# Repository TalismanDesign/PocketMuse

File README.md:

# PocketMuse

Music player app for the PocketMage PDA. Streams MP3 from SD through the OS
audio service, using the built-in PWM piezo or a USB Audio Class speaker.
Supports library browsing, now-playing with album art, playlist management,
shuffle, and loop modes. Runs as a dynamically loaded ELF app on PocketMage OS.

## Build

PocketMuse is an ELF app built against the PocketMage SDK.
Build it with the `pm` CLI from the SDK checkout:

```sh
pm build --pack
```

That compiles `src/`, links `build/PocketMuse.app.elf` plus the
`build/PocketMuse.elfo` overlay, and packs them into `build/PocketMuse.tar`
for installation through the OS app manager. Packaging requires the SDK's
`elf_overlay_relink` and `elf_overlay_emit` tools on `PATH`.

For an ELF-only clean build from this checkout:

```sh
export SDK_ROOT="$(cd ../PocketMage_PDA/Code/PocketMageOS/lib/PocketMage_SDK && pwd)"
make SDK_ROOT="$SDK_ROOT" clean
make SDK_ROOT="$SDK_ROOT" elf
```

The SDK build recipe locates the installed Espressif Xtensa C++ toolchain.
Build the matching host from `PocketMage_PDA/Code/PocketMageOS` with
`pio run -e PM_BETA`. The host must export the playback-request, image-region,
SD-stream, drawing, and activity APIs used by this app.

`mp3` files live in `/music/` at the root of the SD card; the app creates that
directory along with `/music/.muse/` on first launch.

## Key bindings

| Input        | Action                     |
|--------------|----------------------------|
| LEFT / RIGHT | Navigate list / skip track |
| UP / DOWN    | Volume (Now Playing)       |
| SPACE        | Play / pause               |
| ENTER        | Select / play              |
| P            | Cycle source in browser; show queue from Now Playing |
| F            | Toggle favorite            |
| S            | Toggle shuffle             |
| L            | Cycle loop (None/One/All)  |
| D            | Remove selected favorite / playlist entry; keep the music file |
| U            | Output: Auto / Piezo / USB  |
| B            | Switch browser / Now Playing; return from queue |
| ?            | Help overlay               |
| ESC / A      | Exit to PocketMage OS      |

Touch scroll on the slider controls volume in all modes.

## Playback and storage

- Auto selects a connected UAC speaker; Piezo forces the built-in output.
  USB falls back to piezo when no compatible speaker is available. The USB
  status chip appears only while USB is the active playback output.
- Volume and output preference are shared SDK settings in NVS (`PMAudio`). Favorites use
  an absolute-path list; playlists are `.m3u` files under
  `/music/.muse/playlists/`, with one absolute SD path per entry. Blank lines,
  comments, LF, and CRLF are supported. Empty sources remain browsable.
- Natural EOF advances once. Repeat-one affects automatic progression;
  manual next still skips. Shuffle stops after its cycle unless repeat-all
  is enabled. Favorite edits outside the active source preserve the current
  shuffle cycle; a missing playing track keeps the not-found index at `-1`.
- ID3v2.3/v2.4 tags and embedded JPEG/PNG cover regions are read by the SDK's
  streaming media service. The OS decodes covers into a 1-bit image buffer. Unsupported/missing artwork
  uses the app's fallback display.
- The OLED uses decoded PCM frame timing for elapsed playback. Total duration
  comes from MPEG headers, including Xing/VBRI when present, with a bitrate
  estimate when an exact duration is unavailable.
- Idle sleep belongs to the OS and uses its `TIMEOUT` setting. Native and ELF
  input reset the same timer. Playback, open SD streams, USB audio presence,
  USB mode, and OS timeout-inhibition flags keep the device awake.

## Architecture

PocketMuse calls the SDK C ABI; it does not link Arduino or audio/display
drivers. The host owns Espressif `esp_audio_codec`, `pwm_audio`, `usb_stream`,
JPEGDEC/PNGdec, GxEPD2, U8g2, SD access, and sleep management.

Playback queries, metadata/cover probing, image-region decoding, SD operations,
and canvas primitives are generated wrappers over native SDK services. The SDK
owns PCM gain, timing, shared audio settings, and metadata parsing. PocketMuse
owns its library, playlist, shuffle, and presentation state. The SDK retains
ABI 2 adapters for existing apps.

USB serial is the default connector role. Piezo and unattached Auto sessions
retain it; an attached accessory receives one bounded UAC probe. An unsupported
device can then be tried as a keyboard. App exit waits for audio cleanup while
its callbacks and code remain resident.

## Native tests

```sh
python3 tests/run.py
```

Requires Python 3 and a C++17 compiler with AddressSanitizer and UBSan. `CXX`
selects the compiler; `SDK_ROOT` overrides the adjacent SDK checkout. The
tests exercise playlist parsing/mutation, shuffle continuity, playback progression, source
cycling, output preference, playback request results, and idle-timer rollover
and inhibition. They use in-memory SD files and require no device.

USB enumeration/hotplug, audible output, album-art rendering, both displays,
and deep sleep still require validation on a PocketMage device.

## Project layout

```text
src/
   main.cpp             app entry, input and render loop
   muse.cpp             app-wide globals
   library.cpp          SD card track scanner (/music/)
   playlist.cpp         playlist manager (favorites, .m3u)
   ui_player.cpp        playback control, shuffle, shared media-service queries
   ui/
      ui_browser.cpp    library/favorites/playlist browser
      ui_nowplaying.cpp now-playing screen with album art
      ui_playlist.cpp   playlist queue view
      ui_helpers.cpp    header/footer/scrollbar/OLED/time formatting
include/                public headers
tests/                  native regression suites and in-memory SD support
design/                 chosen display mockups
```

## License

Apache-2.0. Same as the PocketMage project.

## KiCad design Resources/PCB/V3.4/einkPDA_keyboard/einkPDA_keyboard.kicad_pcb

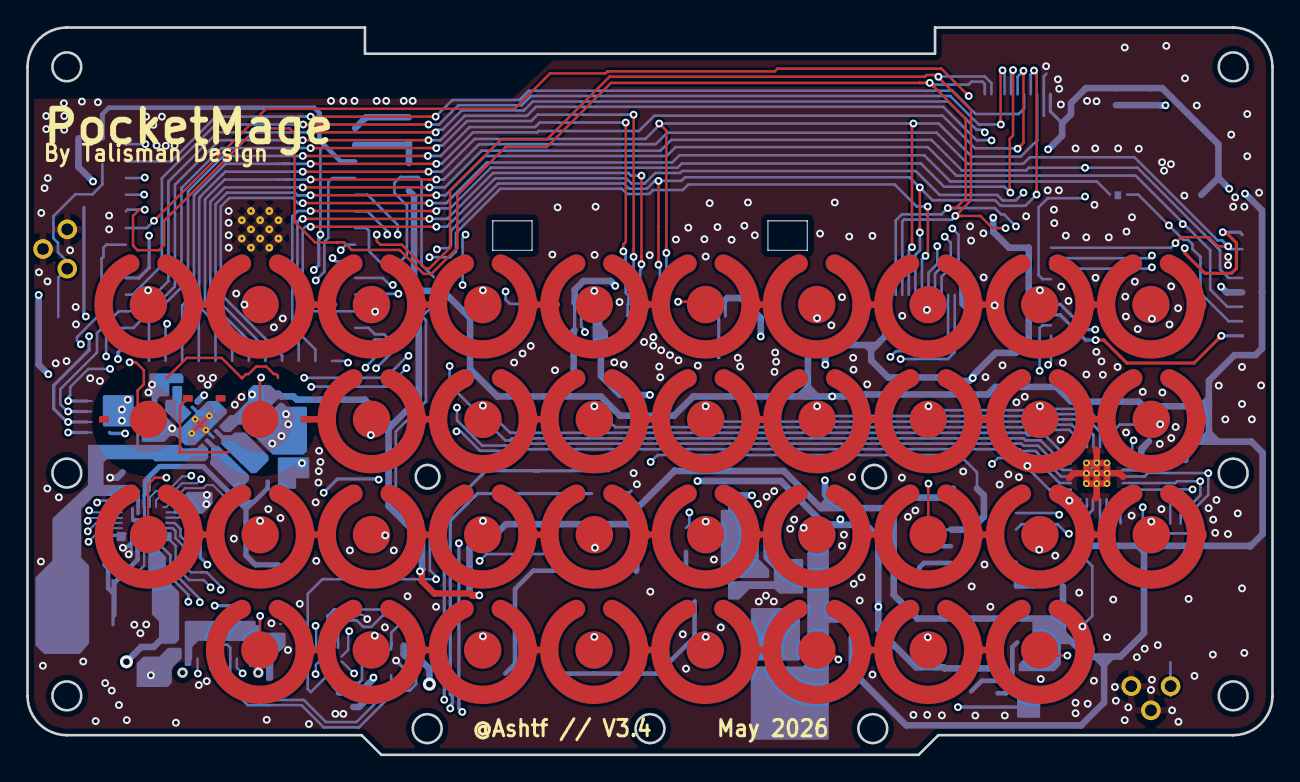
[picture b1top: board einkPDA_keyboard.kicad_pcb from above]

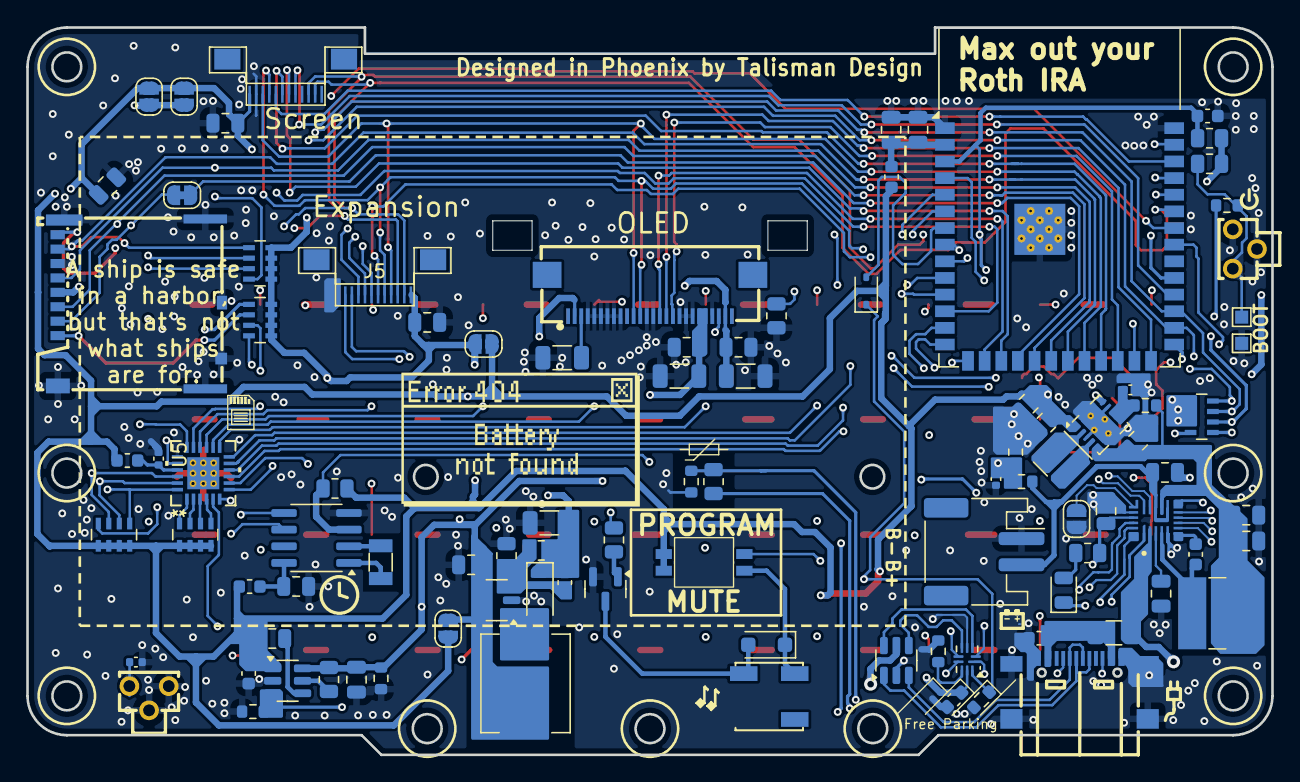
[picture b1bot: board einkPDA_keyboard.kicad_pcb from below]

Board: 4 copper layers, 95.0 x 55.5 mm, 135 parts (97 on the bottom side), 102 nets.

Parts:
BZ1: Buzzer; BUZ-SMD_3P_L5.0-W5.0-P3.50-TL
C1, C4, C6, C20: 1uF; C_0603_1608Metric
C2, C9: 100nF; C_0805_2012Metric
C3, C21, C22: 22uF; C_0805_2012Metric
C5: 47uF; C_0805_2012Metric
C7, C8, C19, C33: 0.1uF; C_0402_1005Metric
C10, C23, C24, C26, C28, C29, C30, C31, C32: 10uF; C_0805_2012Metric
C11: 4.7pF; C_0603_1608Metric
C12, C13, C14, C16: 4.7uF; C_1206_3216Metric
C15, C17: .1uF; C_0805_2012Metric
C18: 680pF; C_0805_2012Metric
C25: 4.7uF; C_0805_2012Metric
C27: 22nF; C_0603_1608Metric
D1: KT-0805Y; LED_0805_2012Metric
D2: MBR0530; D_SOD-123
D3: SM4007; D_SOD-123F
D5: D_Schottky; D_SOD-323
F1: SMD1206-500-6V; Fuse_1206_3216Metric
FB1, FB2, FB3: FerriteBead; L_0603_1608Metric
J1: USB_C_Receptacle_USB2.0_16P; USB-TYPE-C-SMD_TYPE-C-16P-QTWT
J2, J5: Conn_01x12_Pin; AFC01-S12FCA-00
J3: Conn_01x26_Pin; FPC-SMD_AFC24-S26FIA [DUAL-SIDE]
J4: Micro_SD_Card; TF-SMD_503398-1892
JP1: SolderJumper_2_Bridged; SolderJumper-2_P1.3mm_Bridged_RoundedPad1.0x1.5mm
JP2, JP6, JP7, JP8, JP9: SolderJumper_2_Open; SolderJumper-2_P1.3mm_Open_RoundedPad1.0x1.5mm
L1: 10uH; L_Chilisin_BMRx00060630
L2: 1uH; L_Ferrocore_DLG-0504
L3: 2.2uH; L_Wurth_WE-LQSH-3012
Q1: MMBT3904; SOT-23
R1, R14: 10K; R_0805_2012Metric
R2, R8: 100R; R_0603_1608Metric
R3: 4.7k; R_0603_1608Metric
R4: 1k; R_0603_1608Metric
R5, R15: 470R; R_0805_2012Metric
R6, R7, R19: 100K; R_0603_1608Metric
R11, R16: 2k; R_0805_2012Metric
R12: 1.8M; R_0805_2012Metric
R13: 205k; R_0805_2012Metric
R17: 10k; R_0805_2012Metric
R18: 10k; R_0603_1608Metric
R20: 680k; R_0805_2012Metric
RN1, RN2, RN3, RN4, RN5: 4x10k; R_Array_Concave_4x0603
SW1, SW3, SW5, SW6, SW7, SW9, SW10, SW11, SW12, SW13, SW14, SW15, SW16, SW17, SW18, SW19, SW20, SW21, SW22, SW23, SW24, SW25, SW26, SW27, SW28, SW29, SW30, SW31, SW32, SW33, SW34, SW35, SW37, SW38, SW39, SW40: contact_pad_SINGLE
SW2: contactPad_cutoutR
SW4: SW_DIP_x02; 2X_DIP_DHN-02-V-TR
SW8: contactPad_cutoutL
SW36, SW41: YTS-C017-2B; KEY-TH_3P-L4.5-W4.5-P3.0-EH
TH1: NTC; R_0603_1608Metric
TP1, TP2: TestPoint; TestPoint_Pad_1.0x1.0mm
U1: ESP32-S3-WROOM-1-N16R2; ESP32-S3-WROOM-1
U2: USBLC6-2SC6; SOT-23-6
U3: TPS63001; Texas_DRC0010J_ThermalVias
U4: PCF8563T; SOIC-8_3.9x4.9mm_P1.27mm
U5: TCA8418RTWR; RTW24_2P45X2P45
U6: C2764211; JST_PH_2P_P2.00mm
U7: TPS61040DBV; SOT-23-5
U8: TPS22917DBV; SOT-23-6
U9: MP2722GRH-0000-Z; IC_MP2722GRH-0000-Z
U10: TS3USB30ERSWR; UQFN-10_1.4x1.8mm_P0.4mm
Y1: Crystal_32.768kHz; Crystal_SMD_3215-2Pin_3.2x1.5mm

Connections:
+3.3V: C4.2, C6.2, C18.1, C31.2, C32.2, FB1.1, FB2.2, FB3.1, JP2.2 (B), JP7.2 (B), JP8.2 (B), JP9.2 (B), R1.1, R11.2, R14.1, RN1.1 (R1.1), RN1.2 (R2.1), RN1.3 (R3.1), RN1.4 (R4.1), RN2.5 (R4.2), RN2.6 (R3.2), RN2.7 (R2.2), RN2.8 (R1.2), RN4.5 (R4.2), RN4.6 (R3.2), RN4.7 (R2.2), SW4.1, SW4.2, U3.1 (VOUT), U3.10 (FB), U8.1 (VIN), U10.9 (VCC)
+12V: C11.2, C12.1, C13.1, C15.1, D2.1 (K), J3.2, J3.25, R12.1
BAT+: C26.2, R6.1, U6.3 (BATT+), U9.12 (BATTSNS), U9.14 (BATT)
BAT_MEAS: C19.1, R6.2, R7.1, U1.4 (IO4)
BMS_INT: RN4.4 (R4.1), U1.33 (IO40), U9.8 (~INT)
BOOT: R8.1, R14.2, SW36.1, TP1.1
BUZZER: R15.1, U1.10 (IO17)
BZ_CUTOFF: BZ1.1 (+), D3.1 (K), SW4.3
E-PAPER_BUSY: J2.5, U1.30 (IO37)
E-PAPER_CS: J2.8, U1.38 (IO2)
E-PAPER_D/C: J2.7, U1.23 (IO21)
E-PAPER_RES: J2.6, U1.17 (IO9)
EN: C1.2, C33.1, R1.2, SW41.1, U1.3 (EN)
ESP_D+: U1.14 (IO20), U10.2 (D2+)
ESP_D-: U1.13 (IO19), U10.6 (D2-)
EX_A: J5.7, U1.15 (IO3)
EX_B: J5.8, U1.11 (IO18)
EX_C: J5.9, U1.34 (IO41)
GND: C1.1, C2.1, C3.1, C4.1, C5.2, C6.1, C7.2, C8.2, C9.1, C10.1, C12.2, C13.2, C14.2, C15.2, C16.2, C17.2, C19.2, C20.1, C21.1, C22.1, C23.1, C24.2, C25.2, C26.1, C28.1, C29.1, C30.1, C31.1, C32.1, C33.2, J1.A1 (GND), J1.A12 (GND), J1.S1 (SHIELD), J2.11, J3.4, J3.5, J3.6, J3.7, J3.8, J3.9, J3.13, J3.14, J3.18, J3.19, J3.20, J3.23, J4.6 (VSS), J4.9 (SHIELD), J5.12, JP6.1 (A), Q1.2 (E), R3.2, R4.2, R7.2, R13.2, R18.2, R19.2, R20.2, SW36.2, SW36.3 (GND), SW41.2, SW41.3 (GND), TH1.2, TP2.1, U1.1 (GND), U1.40 (GND), U1.41 (GND), U2.2 (GND), U3.3 (PGND), U3.9 (GND), U3.11 (PGND), U4.4 (VSS), U5.19 (GND), U5.25 (EPAD), U6.1 (BATT-), U7.2 (GND), U8.2 (GND), U9.5 (PGND), U9.18 (AGND), U10.4 (GND)
I2C_SCL: RN1.6 (R3.2), RN4.2 (R2.1), U1.28 (IO35), U4.6 (SCL), U5.23 (SCL), U9.16 (SCL)
I2C_SCL_SWITCHED: J2.3, J5.3, RN5.7 (R2.2), U1.25 (IO48)
I2C_SDA: RN1.7 (R2.2), RN4.3 (R3.1), U1.29 (IO36), U4.5 (SDA), U5.22 (SDA), U9.15 (SDA)
I2C_SDA_SWITCHED: J2.2, J5.2, RN5.8 (R1.2), U1.35 (IO42)
IC_D+: U9.21 (D+), U10.1 (D1+)
IC_D-: U9.20 (D-), U10.7 (D1-)
KB_INT: RN1.5 (R4.2), U1.12 (IO8), U5.24 (*INT)
LOAD: R19.1, U1.31 (IO38), U8.3 (ON)
unnamed: BZ1.2 (-), D3.2 (A), Q1.3 (C)
unnamed: C20.2, F1.1, J1.A4 (VBUS), J1.A9 (VBUS)
unnamed: D1.2 (A), R16.1
unnamed: D1.1 (K), U9.11 (STAT/IB)
unnamed: D2.2 (A), L1.2, U7.1 (SW)
unnamed: D5.1 (K), R18.1, SW4.4, U10.10 (S)
unnamed: J1.A5 (CC1), U9.1 (CC1)
unnamed: J1.B5 (CC2), U9.22 (CC2)
unnamed: J1.A6 (D+), J1.B6 (D+), U2.1 (I/O1)
unnamed: J1.A7 (D-), J1.B7 (D-), U2.3 (I/O2)
unnamed: C14.1, J3.3
unnamed: J3.24, R20.1
unnamed: J4.2 (DAT3/CD), JP1.2 (B), RN3.7 (R2.2)
unnamed: JP6.2 (B), U9.17 (~RST)
unnamed: Q1.1 (B), R15.2
unnamed: RN1.8 (R1.2), U5.20 (*RESET)
unnamed: RN2.1 (R1.1), U5.4 (ROW4)
unnamed: RN2.2 (R2.1), U5.3 (ROW5)
unnamed: RN2.3 (R3.1), U5.2 (ROW6)
unnamed: RN2.4 (R4.1), U5.1 (ROW7)
unnamed: RN4.1 (R1.1), U9.9 (PG/NTC2)
unnamed: C25.1, R16.2, RN4.8 (R1.2), U9.19 (VCC)
unnamed: C2.2, C3.2, FB1.2, U1.2 (3V3)
unnamed: R8.2, U1.27 (IO0)
unnamed: C7.1, R2.1, U3.6 (EN), U3.7 (PS/SYNC), U3.8 (VINA)
unnamed: L3.1, U3.4 (L1)
unnamed: L3.2, U3.2 (L2)
unnamed: U4.1 (OSCI), Y1.1
unnamed: U4.2 (OSCO), Y1.2
unnamed: C9.2, FB3.2, U4.8 (VDD)
unnamed: C8.1, FB2.1, U5.21 (VCC)
unnamed: C11.1, R12.2, R13.1, U7.3 (FB)
unnamed: C18.2, U8.4 (CT)
unnamed: R5.2, U8.5 (QOD)
unnamed: C27.2, U9.6 (BST)
unnamed: R17.1, TH1.1, U9.10 (NTC1)
unnamed: C23.2, U9.3 (PMID)
unnamed: C27.1, L2.1, U9.4 (SW)
unnamed: R17.2, U9.7 (VRNTC)
unnamed: R3.1, U10.8 (~OE)
OLED_CS: J3.17, U1.24 (IO47)
OLED_D/C: J3.15, U1.16 (IO46)
OLED_RES: J3.16, U1.26 (IO45)
RTC_INT: R11.1, U1.39 (IO1), U4.3 (~INT)
RX: J5.11, U1.36 (RXD0)
SD_CLK: J4.5 (CLK), RN3.8 (R1.2), U1.20 (IO12)
SD_CMD: J4.3 (CMD), RN3.6 (R3.2), U1.19 (IO11)
SD_CS: JP1.1 (A), U1.18 (IO10)
SD_D0: J4.7 (DAT0), RN3.5 (R4.2), U1.21 (IO13)
SD_D1: J4.8 (DAT1), RN5.5 (R4.2), U1.5 (IO5)
SD_D2: J4.1 (DAT2), RN5.6 (R3.2), U1.6 (IO6)
SPI_MISO_SWITCHED: J5.6, U1.9 (IO16)
SPI_MOSI_SWITCHED: J2.10, J3.11, J5.4, U1.22 (IO14)
SPI_SCK_SWITCHED: J2.9, J3.12, J5.5, U1.8 (IO15)
TX: J5.10, U1.37 (TXD0)
USB_5V: F1.2, U2.5 (VBUS), U9.2 (IN)
USB_D+: U2.6 (I/O1), U10.3 (D+)
USB_D-: U2.4 (I/O2), U10.5 (D-)
USB_SW: D5.2 (A), U1.7 (IO7)
V_LOADSWITCH: C5.1, C10.2, C16.1, C17.1, C21.2, C22.2, C24.1, J2.12, J3.21, J3.22, J4.4 (VDD), J5.1, JP2.1 (A), JP7.1 (A), JP8.1 (A), JP9.1 (A), L1.1, R4.1, R5.1, RN3.1 (R1.1), RN3.2 (R2.1), RN3.3 (R3.1), RN3.4 (R4.1), RN5.1 (R1.1), RN5.2 (R2.1), RN5.3 (R3.1), RN5.4 (R4.1), U7.4 (EN), U7.5 (VIN), U8.6 (VOUT)
V_SYS: C28.2, C29.2, C30.2, L2.2, R2.2, U3.5 (VIN), U9.13 (SYS)
col1: SW1.1, SW2.1, SW3.1, U5.9 (COL0)
col2: SW7.1, SW8.1, SW9.1, SW10.1, U5.10 (COL1)
col3: SW13.1, SW14.1, SW15.1, SW16.1, U5.11 (COL2)
col4: SW19.1, SW20.1, SW21.1, SW22.1, U5.12 (COL3)
col5: SW25.1, SW26.1, SW27.1, SW28.1, U5.13 (COL4)
col6: SW31.1, SW32.1, SW33.1, SW34.1, U5.14 (COL5)
col7: SW37.1, SW38.1, SW39.1, SW40.1, U5.15 (COL6)
col8: SW5.1, SW6.1, SW11.1, SW12.1, U5.16 (COL7)
col9: SW17.1, SW18.1, SW23.1, SW24.1, U5.17 (COL8)
col10: SW29.1, SW30.1, SW35.1, U5.18 (COL9)
row1: SW1.2, SW5.2, SW7.2, SW13.2, SW17.2, SW19.2, SW25.2, SW29.2, SW31.2, SW37.2, U5.8 (ROW0)
row2: SW2.2, SW6.2, SW8.2, SW14.2, SW18.2, SW20.2, SW26.2, SW30.2, SW32.2, SW38.2, U5.7 (ROW1)
row3: SW3.2, SW9.2, SW11.2, SW15.2, SW21.2, SW23.2, SW27.2, SW33.2, SW35.2, SW39.2, U5.6 (ROW2)
row4: SW10.2, SW12.2, SW16.2, SW22.2, SW24.2, SW28.2, SW34.2, SW40.2, U5.5 (ROW3)

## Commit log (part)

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2026-06-19 Symlinks
2026-06-19 Kinda wip core
2026-06-19 Whaddya know, it crashes :/
2026-06-19 It loads but doesn't play, oh joy
2026-06-19 Improvements, still no playing
2026-06-19 I can hear only static
2026-06-19 Yeah i thought this would work NOPE
2026-06-20 I mean it kinda works but it's not 2x speed or maybe it is
    but it's like parts of the mp3 is skipped
2026-06-20 THE ENTIRE AUDIO IS THERE
2026-06-20 Full song plays now but it's fast but this is so fragileee
2026-06-20 I give up on manual
2026-06-20 AAAA STATIC ARE YOU KIDDING MEEEEE
2026-06-20 I can hear it... but it's kinda quiet and slow
2026-06-21 Hey it's a bit louder
    BUT PITCH WHY
2026-06-21 YAY IT WORKS
2026-06-21 Bug fixes
2026-06-21 Album art but PNG OMG and a jpeg bugfix
2026-06-21 CI™️
2026-06-21 chore: auto-build PocketMuse.tar
2026-06-21 OH SHOOT README
